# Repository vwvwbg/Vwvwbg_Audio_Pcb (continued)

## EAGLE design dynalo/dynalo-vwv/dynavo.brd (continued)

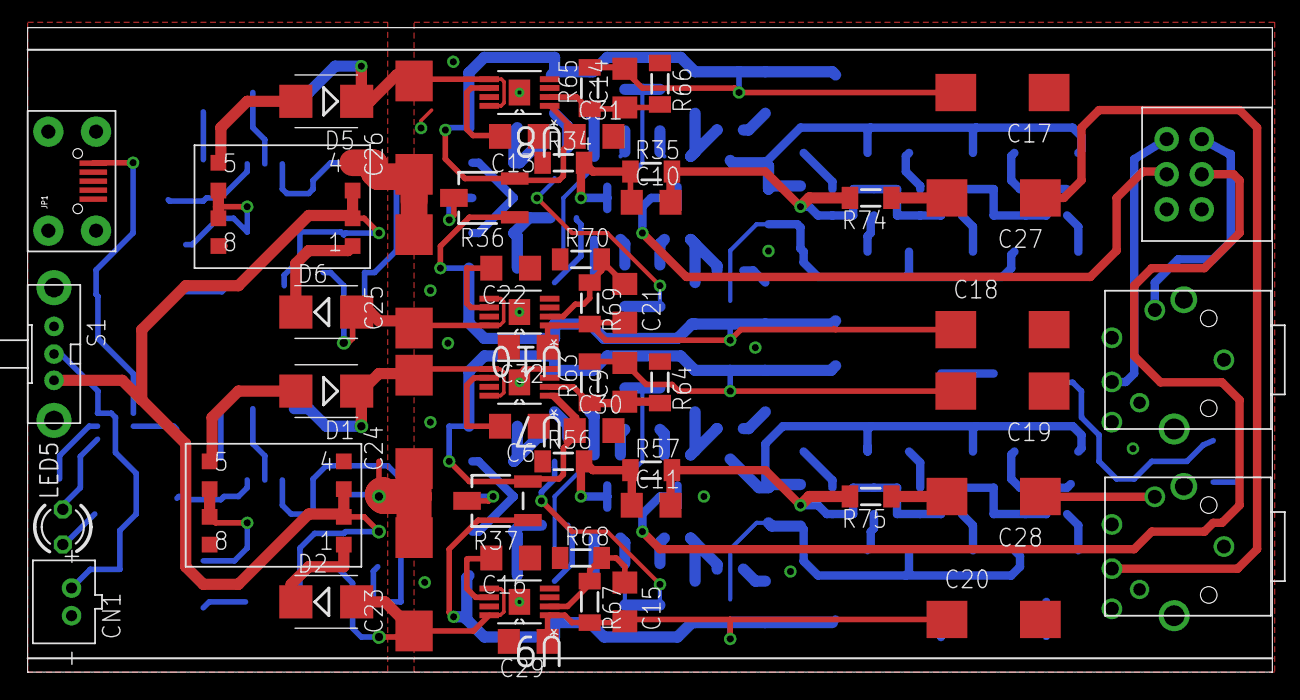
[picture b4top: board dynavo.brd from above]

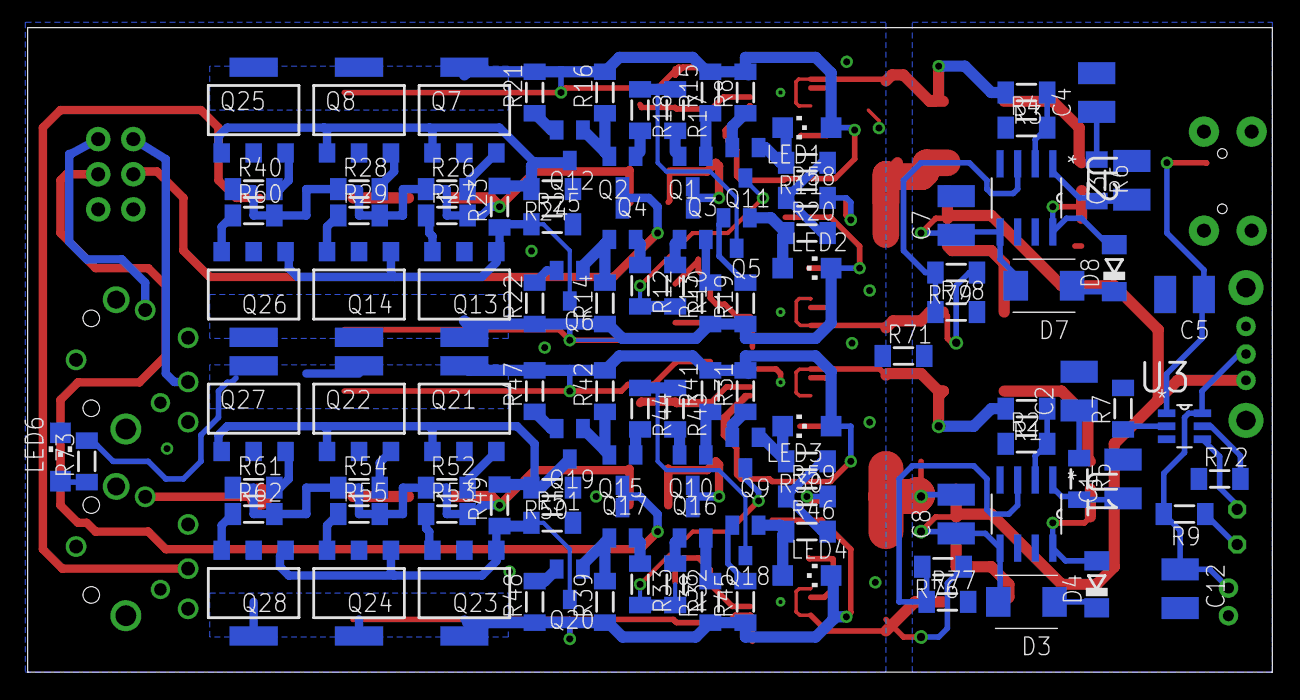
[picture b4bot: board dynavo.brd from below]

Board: 2 copper layers, 90.0 x 46.6 mm, 168 parts (111 on the bottom side), 106 nets.

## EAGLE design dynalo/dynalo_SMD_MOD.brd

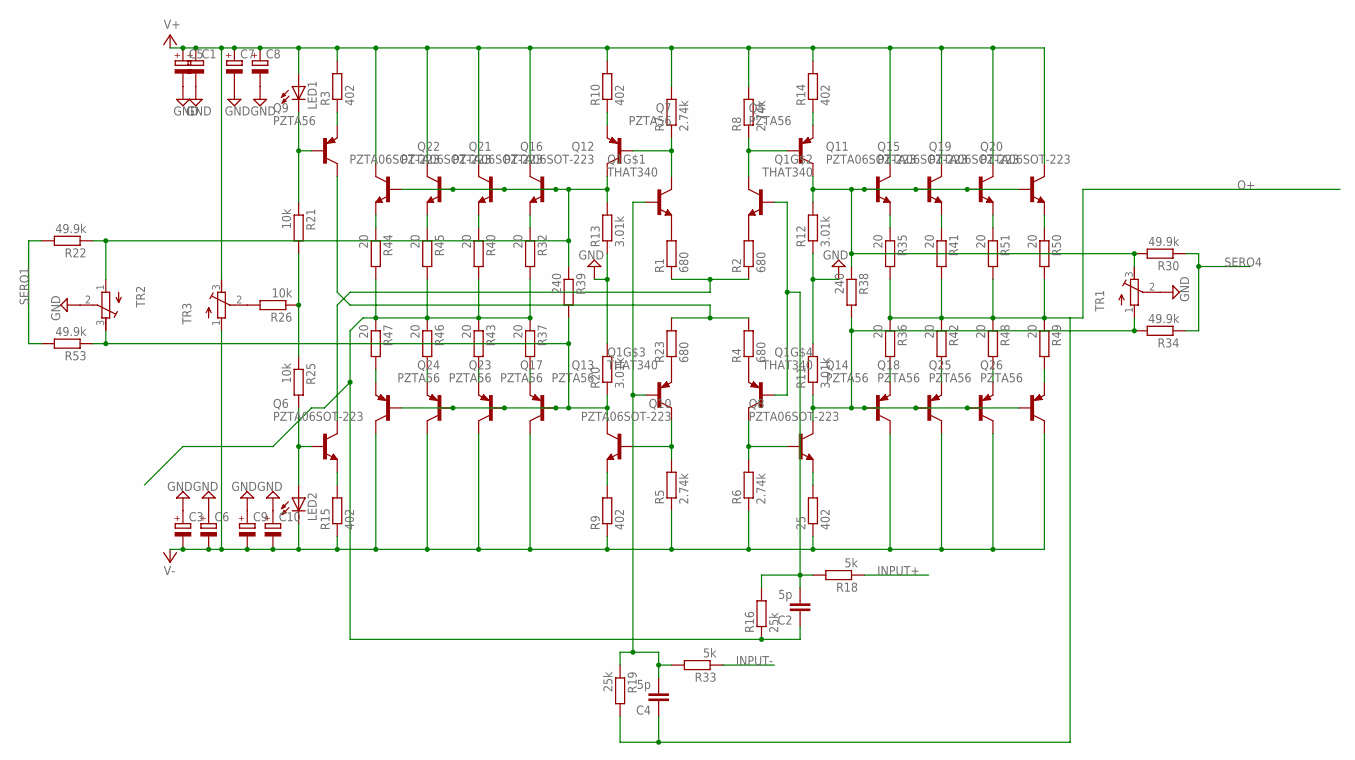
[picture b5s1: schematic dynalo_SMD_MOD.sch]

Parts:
25: 402; MINI_MELF-0204W
C1, C3, C5, C6, C7, C8, C9, C10: CPOL-EUSP-CAP-CX; SP-CAP-CX
C2, C4: 5p; C0805
LED1, LED2: LED5MM
Q1: THAT340; DIP254P762X510-14
Q5, Q7, Q9, Q13, Q14, Q17, Q18, Q23, Q24, Q25, Q26: PZTA56; SOT223
Q6, Q8, Q10, Q11, Q12, Q15, Q16, Q19, Q20, Q21, Q22: PZTA06SOT-223; SOT223
R1, R2, R4, R23: 680; MINI_MELF-0204W
R3, R9, R10, R14, R15: 402; MINI_MELF-0204W
R5, R6, R7, R8: 2.74k; MINI_MELF-0204W
R11, R12, R13, R20: 3.01k; MINI_MELF-0204W
R16, R19: 25k; MINI_MELF-0204W
R18, R33: 5k; MINI_MELF-0204W
R21, R25, R26: 10k; MINI_MELF-0204W
R22, R30, R34, R53: 49.9k; MINI_MELF-0204W
R32, R35, R36, R37, R40, R41, R42, R43, R44, R45, R46, R47, R48, R49, R50, R51: 20; MINI_MELF-0204W
R38, R39: 240; MINI_MELF-0204W
TR1, TR2, TR3: R-TRIMM3296W; RTRIM3296W

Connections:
GND: C1.-, C3.+, C5.-, C6.+, C7.-, C8.-, C9.+, C10.+, R11.2, R12.1, R13.1, R20.2, TR1.2 (S), TR2.2 (S)
INPUT+: R18.1
INPUT-: R33.1
unnamed: Q1.3 (E), R1.2
unnamed: Q1.12 (E), R2.2
unnamed: Q1.5 (E), R23.1
unnamed: Q1.10 (E), R4.1
unnamed: Q1.1 (C), Q7.1 (B), R7.1
unnamed: Q1.14 (C), Q5.1 (B), R8.1
unnamed: Q1.7 (C), Q10.1 (B), R5.2
unnamed: Q1.8 (C), Q8.1 (B), R6.2
unnamed: Q9.2 (C), Q9.4 (C), R4.2, R23.2
unnamed: Q6.2 (C), Q6.4 (C), R1.1, R2.1
unnamed: Q10.3 (E), R9.2
unnamed: Q7.3 (E), R10.1
unnamed: C4.2, Q1.2 (B), Q1.6 (B), R19.1, R33.2
unnamed: C2.2, Q1.9 (B), Q1.13 (B), R16.2, R18.2
unnamed: Q7.2 (C), Q7.4 (C), Q12.1 (B), Q16.1 (B), Q21.1 (B), Q22.1 (B), R13.2, R22.1, R39.1, TR2.1 (A)
unnamed: Q10.2 (C), Q10.4 (C), Q13.1 (B), Q17.1 (B), Q23.1 (B), Q24.1 (B), R20.1, R39.2, R53.1, TR2.3 (E)
unnamed: Q11.3 (E), R35.1
unnamed: Q5.2 (C), Q5.4 (C), Q11.1 (B), Q15.1 (B), Q19.1 (B), Q20.1 (B), R12.2, R30.2, R38.1, TR1.3 (E)
unnamed: 25.2, Q8.3 (E)
unnamed: Q14.3 (E), R36.2
unnamed: Q5.3 (E), R14.1
unnamed: Q9.3 (E), R3.1
unnamed: Q6.3 (E), R15.2
unnamed: Q18.3 (E), R42.2
unnamed: Q15.3 (E), R41.1
unnamed: Q19.3 (E), R51.1
unnamed: Q20.3 (E), R50.1
unnamed: Q25.3 (E), R48.2
unnamed: Q8.2 (C), Q8.4 (C), Q14.1 (B), Q18.1 (B), Q25.1 (B), Q26.1 (B), R11.1, R34.2, R38.2, TR1.1 (A)
unnamed: Q26.3 (E), R49.2
unnamed: R26.2, TR3.2 (S)
unnamed: R21.2, R25.1, R26.1
unnamed: Q22.3 (E), R44.1
unnamed: Q21.3 (E), R45.1
unnamed: Q16.3 (E), R40.1
unnamed: Q12.3 (E), R32.1
unnamed: Q24.3 (E), R47.2
unnamed: Q23.3 (E), R46.2
unnamed: Q17.3 (E), R43.2
unnamed: Q13.3 (E), R37.2
unnamed: LED2.A, Q6.1 (B), R25.2
unnamed: LED1.K (C), Q9.1 (B), R21.1
O+: C4.1, R19.2, R35.2, R36.1, R41.2, R42.1, R48.1, R49.1, R50.2, R51.2
O-: C2.1, R16.1, R32.2, R37.1, R40.2, R43.1, R44.2, R45.2, R46.1, R47.1
SERO1: R22.2, R53.2
SERO4: R30.1, R34.1
V+: C1.+, C5.+, C7.+, C8.+, LED1.A, Q11.2 (C), Q11.4 (C), Q12.2 (C), Q12.4 (C), Q15.2 (C), Q15.4 (C), Q16.2 (C), Q16.4 (C), Q19.2 (C), Q19.4 (C), Q20.2 (C), Q20.4 (C), Q21.2 (C), Q21.4 (C), Q22.2 (C), Q22.4 (C), R3.2, R7.2, R8.2, R10.2, R14.2, TR3.3 (E)
V-: 25.1, C3.-, C6.-, C9.-, C10.-, LED2.K (C), Q13.2 (C), Q13.4 (C), Q14.2 (C), Q14.4 (C), Q17.2 (C), Q17.4 (C), Q18.2 (C), Q18.4 (C), Q23.2 (C), Q23.4 (C), Q24.2 (C), Q24.4 (C), Q25.2 (C), Q25.4 (C), Q26.2 (C), Q26.4 (C), R5.1, R6.1, R9.1, R15.1, TR3.1 (A)

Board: 2 copper layers, 85 parts (9 on the bottom side), 49 nets, no tracks yet.

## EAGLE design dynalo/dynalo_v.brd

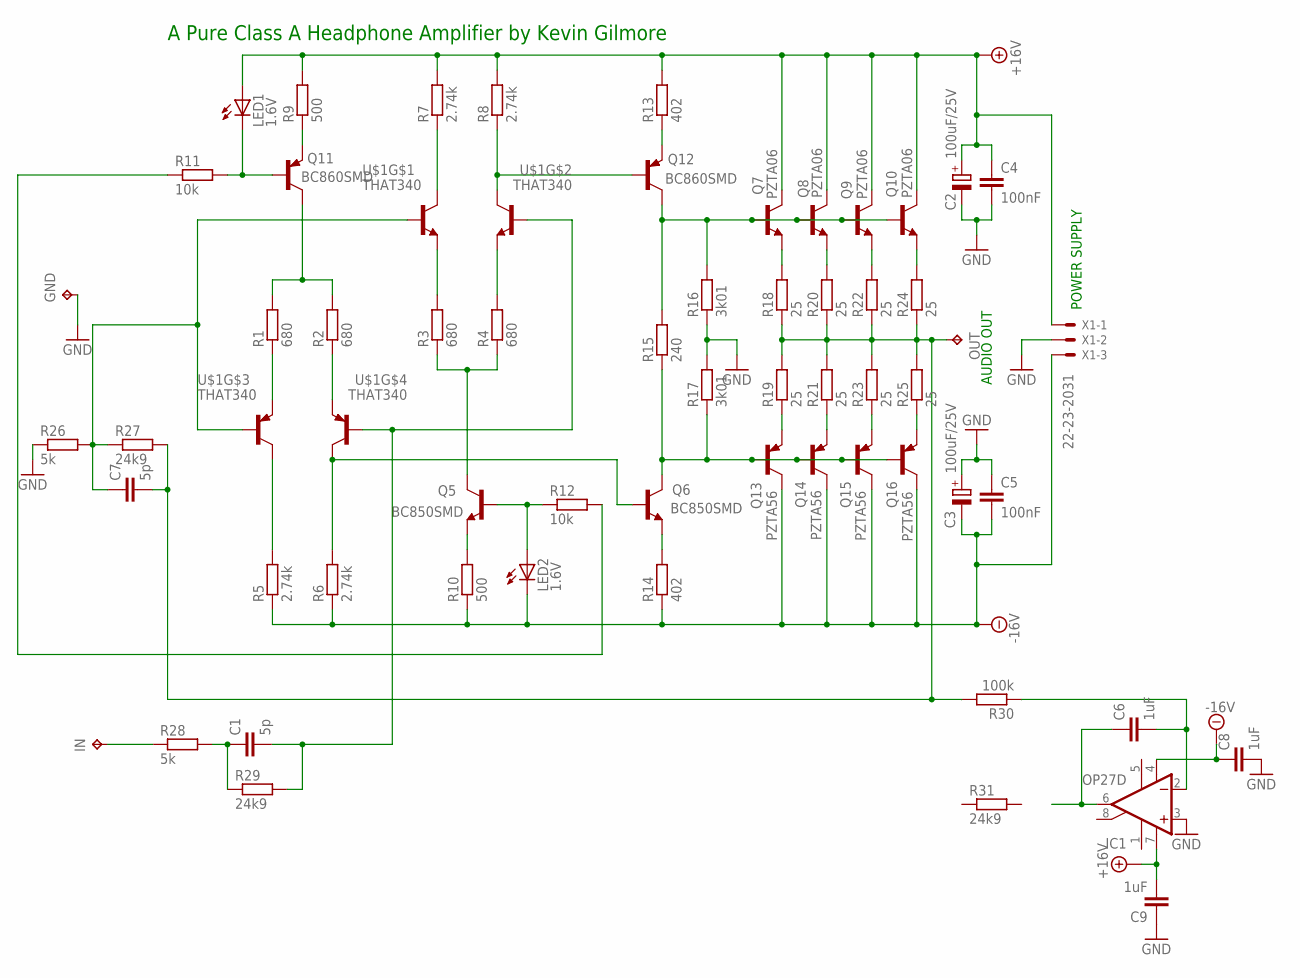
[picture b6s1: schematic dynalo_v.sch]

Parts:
C1, C7: 5p; C1206
C2, C3: 100uF/25V; E3,5-8
C4, C5: 100nF; C050-035X075
C6, C8, C9: 1uF; C1206
GND: TPPAD1-20; P1-20
IC1: OP27D; SO08
IN: TPPAD1-20; P1-20
LED1, LED2: 1.6V; CHIPLED_1206
OUT: TPPAD1-20; P1-20
Q5, Q6: BC850SMD; SOT23-BEC
Q7, Q8, Q9, Q10: PZTA06; SOT223R_INFINEON
Q11, Q12: BC860SMD; SOT23-BEC
Q13, Q14, Q15, Q16: PZTA56; SOT223R_INFINEON
R1, R2, R3, R4: 680; MINI_MELF-0204W
R5, R6, R7, R8: 2.74k; MINI_MELF-0204W
R9, R10: 500; MINI_MELF-0204W
R11, R12: 10k; MINI_MELF-0204W
R13, R14: 402; MINI_MELF-0204W
R15: 240; MINI_MELF-0204W
R16, R17: 3k01; MINI_MELF-0204W
R18, R19, R20, R21, R22, R23, R24, R25: 25; MINI_MELF-0204W
R26, R28: 5k; MINI_MELF-0204W
R27, R29, R31: 24k9; MINI_MELF-0204W
R30: 100k; MINI_MELF-0204W
U$1: THAT340; DIP254P762X510-14
X1: 22-23-2031

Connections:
+15V: C2.+, C4.1, C9.2, IC1.7 (V+), LED1.A, Q7.2 (C), Q7.4 (C), Q8.2 (C), Q8.4 (C), Q9.2 (C), Q9.4 (C), Q10.2 (C), Q10.4 (C), R7.2, R8.2, R9.2, R13.2, X1.1
-15V: C3.-, C5.2, C8.1, IC1.4 (V-), LED2.C, Q13.2 (C), Q13.4 (C), Q14.2 (C), Q14.4 (C), Q15.2 (C), Q15.4 (C), Q16.2 (C), Q16.4 (C), R5.1, R6.1, R10.1, R14.1, X1.3
GND: C2.-, C3.+, C4.2, C5.1, C8.2, C9.1, GND.TP, IC1.3 (+IN), R16.1, R17.2, R26.1, X1.2
unnamed: C7.2, OUT.TP, R18.1, R19.2, R20.1, R21.2, R22.1, R23.2, R24.1, R25.2, R27.2, R30.2
unnamed: Q7.3 (E), R18.2
unnamed: Q8.3 (E), R20.2
unnamed: Q9.3 (E), R22.2
unnamed: Q10.3 (E), R24.2
unnamed: Q13.3 (E), R19.1
unnamed: Q14.3 (E), R21.1
unnamed: Q15.3 (E), R23.1
unnamed: Q16.3 (E), R25.1
unnamed: Q11.E, R9.1
unnamed: Q7.1 (B), Q8.1 (B), Q9.1 (B), Q10.1 (B), Q12.C, R15.2, R16.2
unnamed: LED1.C, Q11.B, R11.2
unnamed: Q6.C, Q13.1 (B), Q14.1 (B), Q15.1 (B), Q16.1 (B), R15.1, R17.1
unnamed: Q12.E, R13.1
unnamed: Q6.E, R14.2
unnamed: Q5.E, R10.2
unnamed: LED2.A, Q5.B, R12.1
unnamed: Q5.C, R3.1, R4.1
unnamed: R7.1, U$1.1 (C)
unnamed: R3.2, U$1.3 (E)
unnamed: R4.2, U$1.12 (E)
unnamed: Q12.B, R8.1, U$1.14 (C)
unnamed: R1.1, U$1.5 (E)
unnamed: Q6.B, R6.2, U$1.8 (C)
unnamed: R2.1, U$1.10 (E)
unnamed: R5.2, U$1.7 (C)
unnamed: Q11.C, R1.2, R2.2
unnamed: C7.1, R26.2, R27.1, U$1.2 (B), U$1.6 (B)
unnamed: IN.TP, R28.1
unnamed: C1.1, R28.2, R29.1
unnamed: C1.2, R29.2, U$1.9 (B), U$1.13 (B)
unnamed: C6.1, IC1.6 (OUT)
unnamed: R11.1, R12.2
unnamed: C6.2, IC1.2 (-IN), R30.1

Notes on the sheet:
A Pure Class A Headphone Amplifier by Kevin Gilmore
AUDIO OUT
POWER SUPPLY

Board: 2 copper layers, 60 parts (13 on the bottom side), 37 nets, no tracks yet.
